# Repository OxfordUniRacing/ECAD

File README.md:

View this project on [CADLAB.io](https://cadlab.io/project/1514). 

# ECAD
Schematics and designs for the electronics team
See notes on project struture in the Oxford Uni Racing ECAD project description.
Built with EAGLE 9.2.2

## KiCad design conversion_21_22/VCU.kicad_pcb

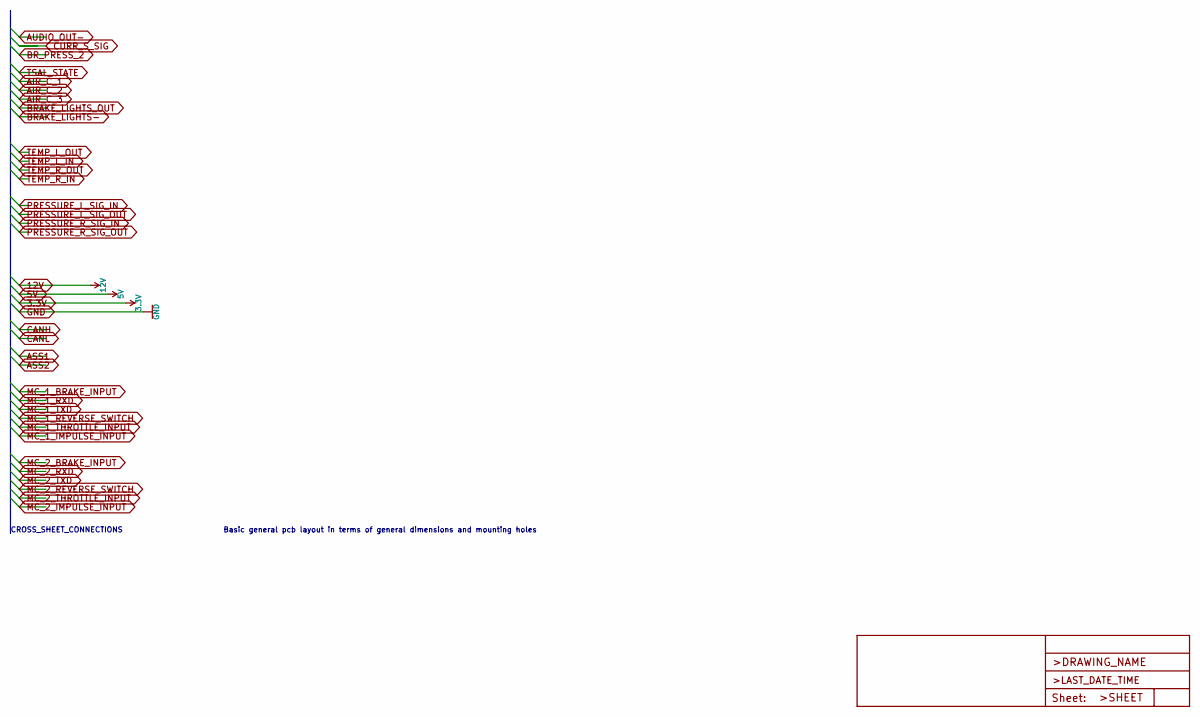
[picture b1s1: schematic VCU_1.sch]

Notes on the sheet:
Basic general pcb layout in terms of general dimensions and mounting holes
CROSS_SHEET_CONNECTIONS

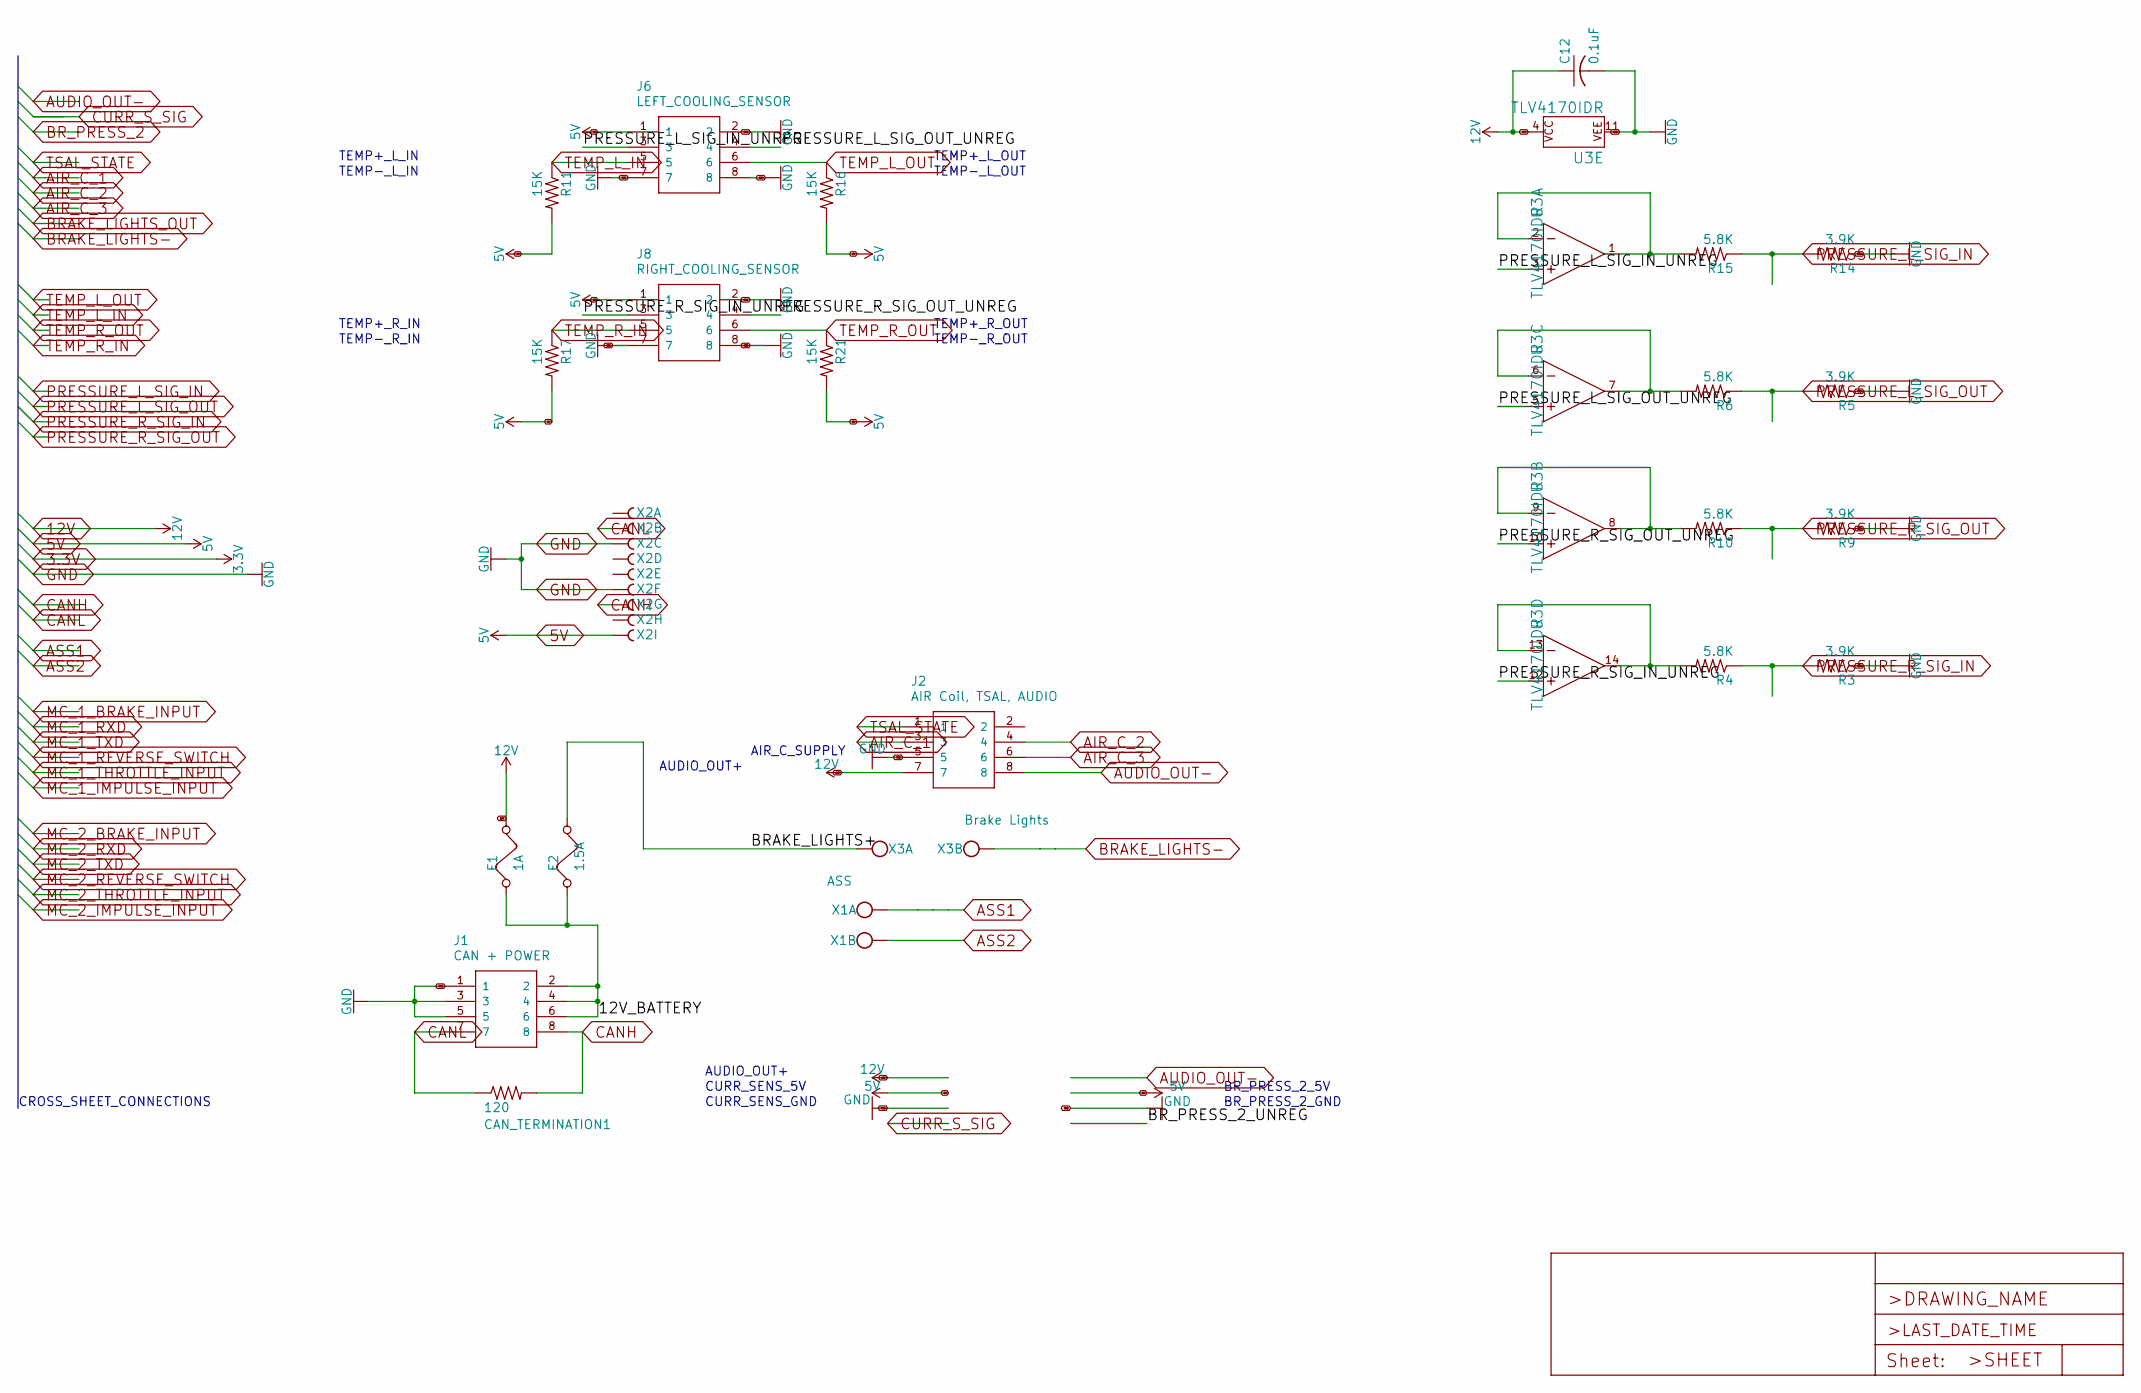
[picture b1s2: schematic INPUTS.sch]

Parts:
C12: 0.1uF; C050-024X044
CAN_TERMINATION1: 120; R0805
F1: 1A; FUSE
F2: 1.5A; FUSE
J1: CAN + POWER; HDRV8W64P254_2X4_1778X895X915P
J2: AIR Coil, TSAL, AUDIO; HDRV8W64P254_2X4_1778X895X915P
J6: LEFT_COOLING_SENSOR; HDRV8W64P254_2X4_1778X895X915P
J8: RIGHT_COOLING_SENSOR; HDRV8W64P254_2X4_1778X895X915P
R3, R5, R9, R14: 3.9K; R0805
R4, R6, R10, R15: 5.8K; R0805
R11, R16, R17, R21: 15K; R0805
U3: TLV4170IDR; SO14
X1: ASS; W237-102
X2: D-SUB9-H2M09ST; H2M09ST
X3: Brake Lights; W237-102

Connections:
5V: J6.1, J8.1, R11.2, R16.2, R17.2, R21.2, X2.9; also elsewhere on the board
12V: C12.1, F1.2, J2.7, U3.4 (P$V+); also elsewhere on the board
/INPUTS/12V_BATTERY: F1.1, F2.1, J1.2, J1.4, J1.6
/INPUTS/BRAKE_LIGHTS+: F2.2, X3.1
/INPUTS/PRESSURE_L_SIG_IN_UNREG: J6.3, U3.3 (+IN)
/INPUTS/PRESSURE_L_SIG_OUT_UNREG: J6.4, U3.5 (+IN)
/INPUTS/PRESSURE_R_SIG_IN_UNREG: J8.3, U3.12 (+IN)
/INPUTS/PRESSURE_R_SIG_OUT_UNREG: J8.4, U3.10 (+IN)
AIR_C_1: J2.3; also elsewhere on the board
AIR_C_2: J2.4; also elsewhere on the board
AIR_C_3: J2.6; also elsewhere on the board
ASS1: X1.1; also elsewhere on the board
ASS2: X1.2; also elsewhere on the board
AUDIO_OUT-: J2.8; also elsewhere on the board
BRAKE_LIGHTS-: X3.2; also elsewhere on the board
CANH: CAN_TERMINATION1.2, J1.8, X2.7; also elsewhere on the board
CANL: CAN_TERMINATION1.1, J1.7, X2.2; also elsewhere on the board
GND: C12.2, J1.1, J1.3, J1.5, J2.5, J6.2, J6.7, J6.8, J8.2, J8.7, J8.8, R3.1, R5.1, R9.1, R14.1, U3.11 (P$V-), X2.3, X2.6; also elsewhere on the board
unnamed: R4.2, U3.13 (-IN), U3.14 (OUT)
unnamed: R6.2, U3.6 (-IN), U3.7 (OUT)
unnamed: R10.2, U3.8 (OUT), U3.9 (-IN)
unnamed: R15.2, U3.1 (OUT), U3.2 (-IN)
PRESSURE_L_SIG_IN: R14.2, R15.1; also elsewhere on the board
PRESSURE_L_SIG_OUT: R5.2, R6.1; also elsewhere on the board
PRESSURE_R_SIG_IN: R3.2, R4.1; also elsewhere on the board
PRESSURE_R_SIG_OUT: R9.2, R10.1; also elsewhere on the board
TEMP_L_IN: J6.5, R11.1; also elsewhere on the board
TEMP_L_OUT: J6.6, R16.1; also elsewhere on the board
TEMP_R_IN: J8.5, R17.1; also elsewhere on the board
TEMP_R_OUT: J8.6, R21.1; also elsewhere on the board
TSAL_STATE: J2.1; also elsewhere on the board

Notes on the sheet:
CROSS_SHEET_CONNECTIONS
TEMP+_L_IN
TEMP-_L_IN
TEMP+_R_IN
TEMP-_R_IN
AIR_C_SUPPLY
CURR_SENS_5V
CURR_SENS_GND
BR_PRESS_2_5V
BR_PRESS_2_GND
AUDIO_OUT+
TEMP+_R_OUT
TEMP-_R_OUT
TEMP-_L_OUT
TEMP+_L_OUT

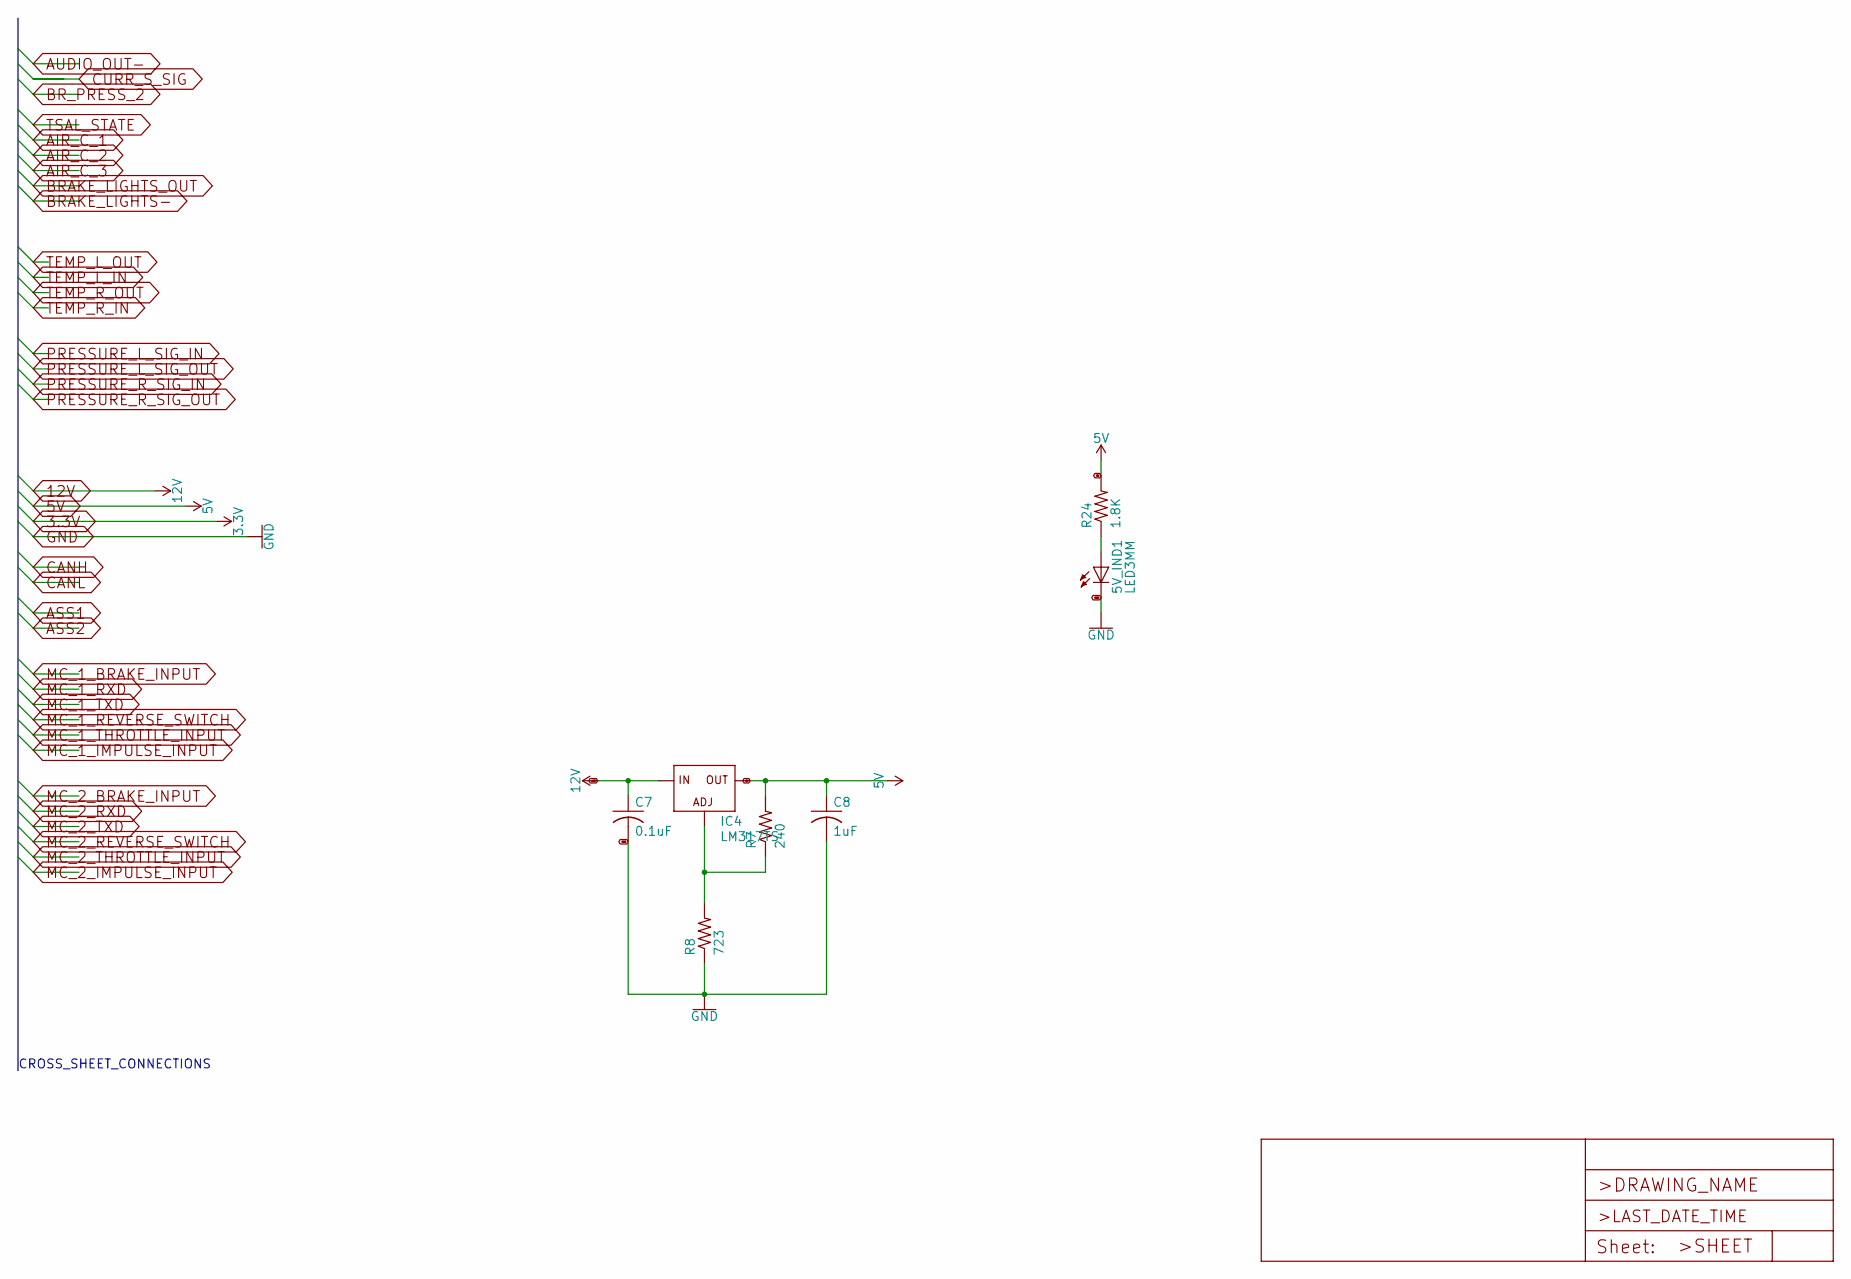
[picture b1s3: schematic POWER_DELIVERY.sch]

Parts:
5V_IND: LED3MM
C7: 0.1uF; C050-025X075
C8: 1uF; C050-025X075
IC4: LM317TS; 317TS
R7: 240; R0805
R8: 723; R0805
R24: 1.8K; R0805

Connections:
5V: C8.1, IC4.2 (OUT), R7.2, R24.2; also elsewhere on the board
12V: C7.1, IC4.3 (IN); also elsewhere on the board
GND: C7.2, C8.2, R8.1; also elsewhere on the board
unnamed 35: R24.1; also elsewhere on the board
unnamed: IC4.1 (ADJ), R7.1, R8.2

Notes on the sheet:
CROSS_SHEET_CONNECTIONS

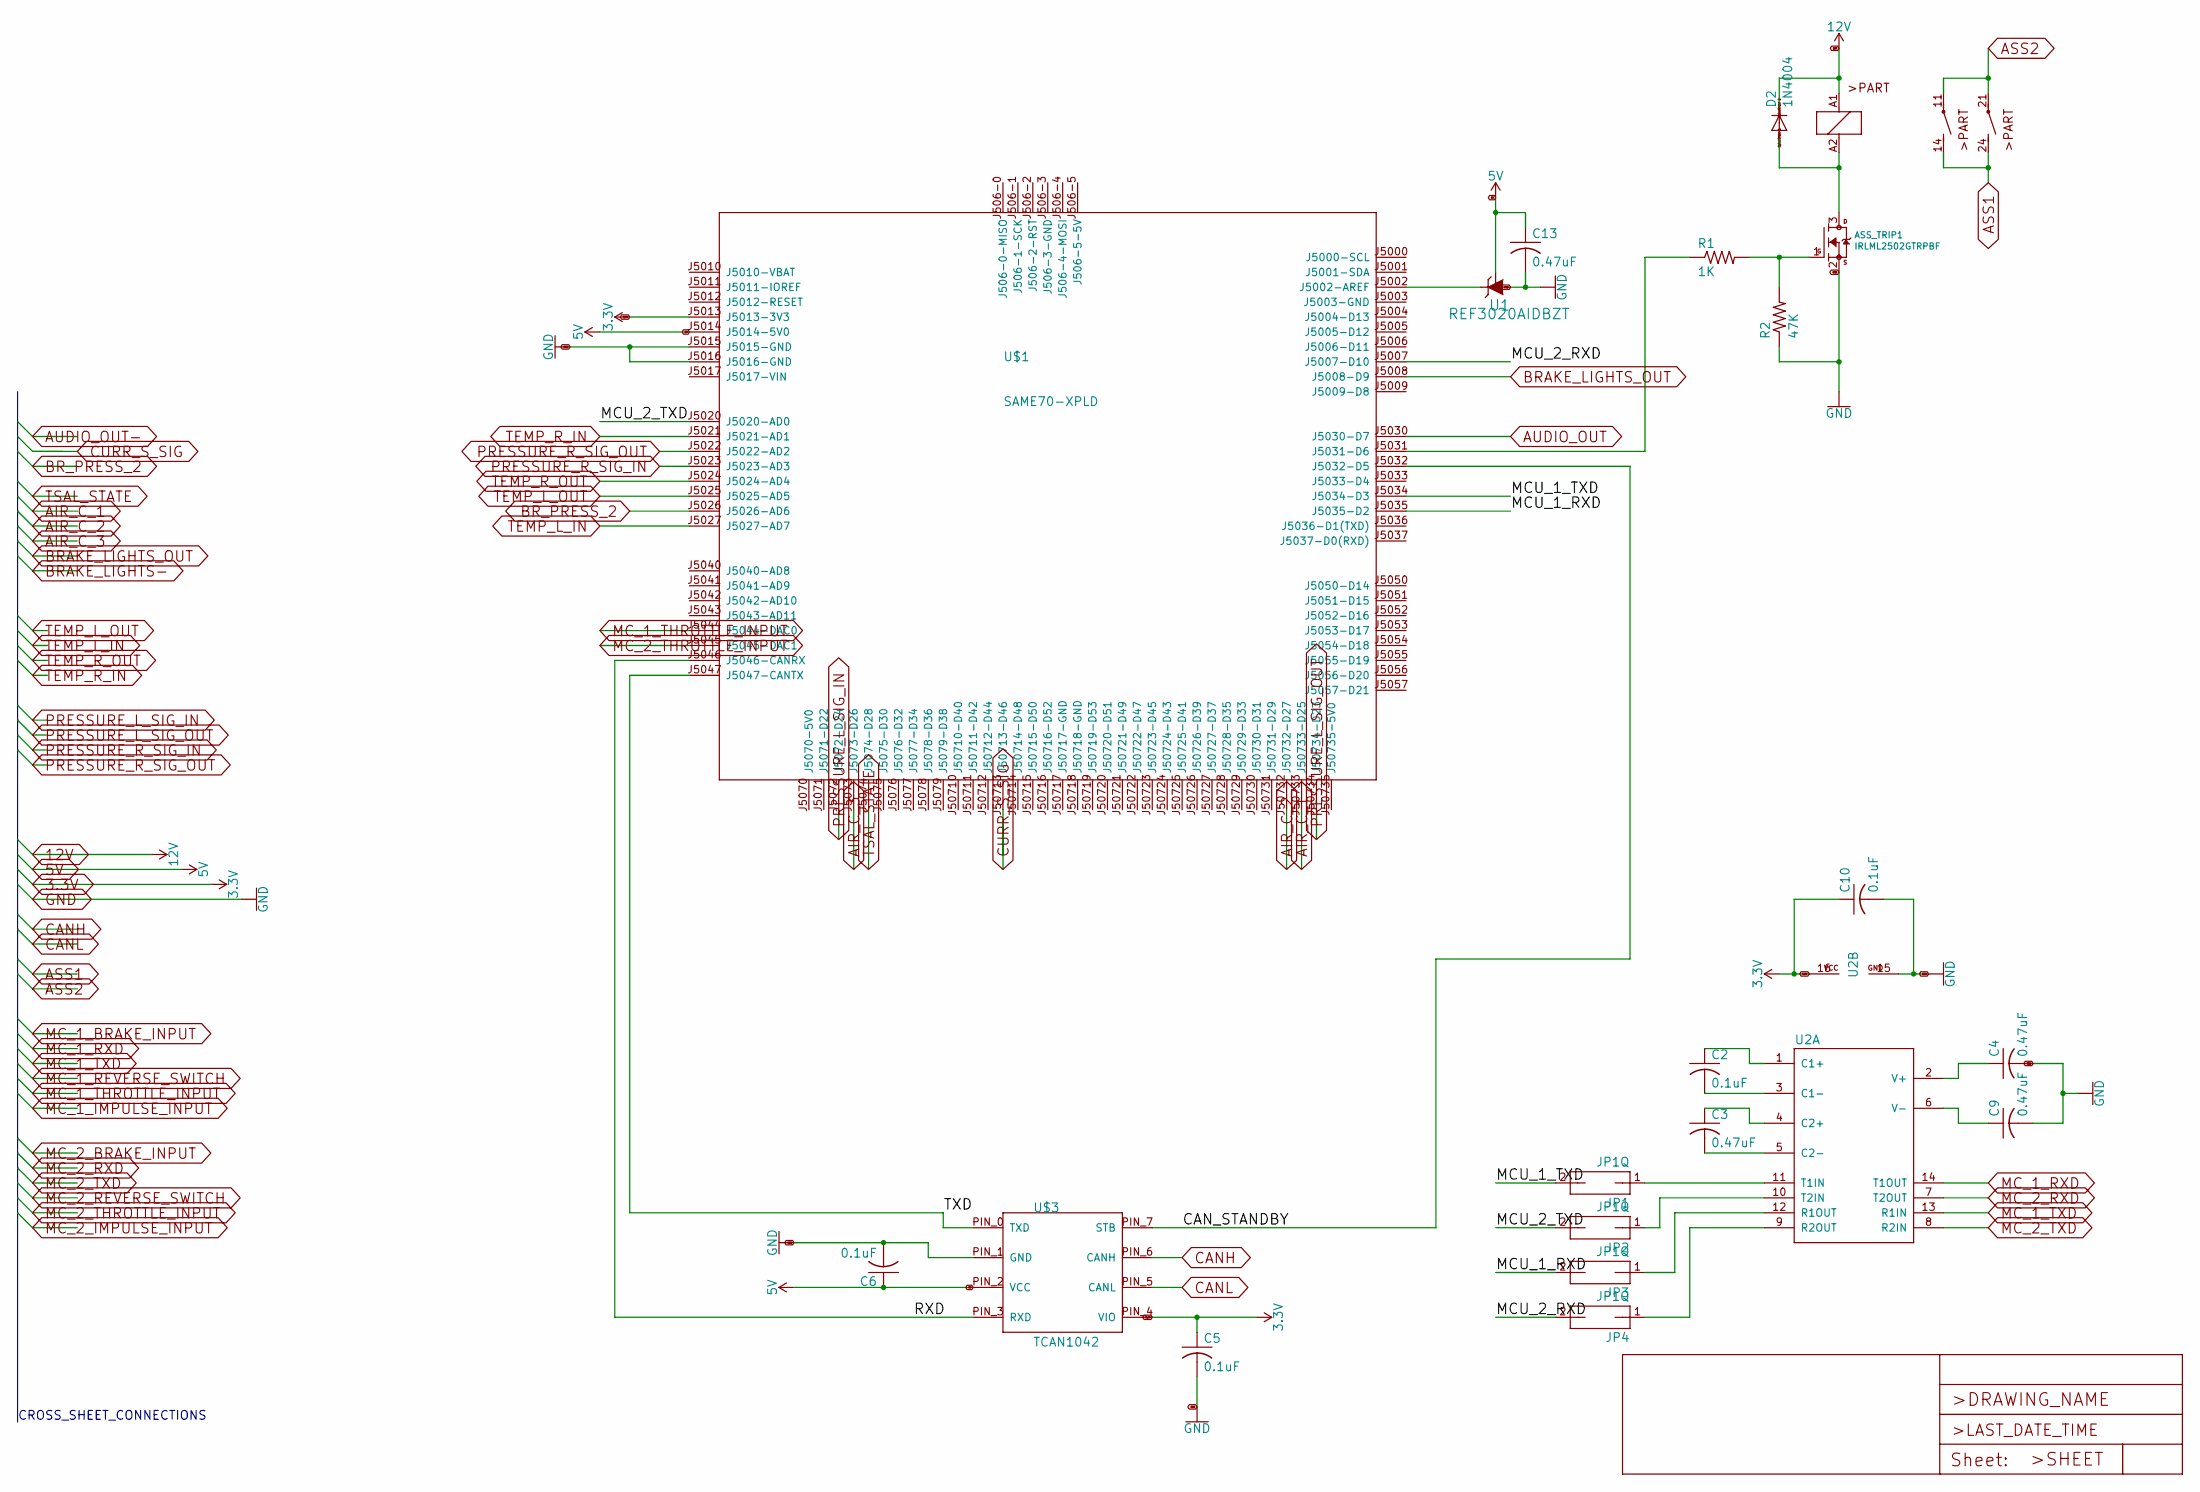
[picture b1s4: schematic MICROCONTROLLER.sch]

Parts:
ASS_TRIP: IRLML2502GTRPBF; SOT23
C2, C5, C6, C10: 0.1uF; C025-024X044
C3, C4, C9: 0.47uF; C025-024X044
C13: 0.47uF; C050-024X044
D2: 1N4004; DO41-10
JP1, JP2, JP3, JP4: JP1Q; JP1
K1: RT44?4; RT2N_O
R1: 1K; R0805
R2: 47K; R0805
U1: REF3020AIDBZT; SOT23-3
U2: MAX3232S; SO16
U$1: SAME70-XPLD
U$3: TCAN1042

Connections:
3.3V: C5.1, C10.1, U2.16 (VCC), U$1.J5013 (J5013-3V3), U$3.PIN_4 (VIO)
5V: C6.1, C13.1, U1.1 (ADJ), U$1.J5014 (J5014-5V0), U$3.PIN_2 (VCC); also elsewhere on the board
12V: D2.C, K1.A1 (1); also elsewhere on the board
/MICROCONTROLLER/CAN_STANDBY: U$1.J5032 (J5032-D5), U$3.PIN_7 (STB)
/MICROCONTROLLER/MCU_1_RXD: JP3.2, U$1.J5035 (J5035-D2)
/MICROCONTROLLER/MCU_1_TXD: JP1.2, U$1.J5034 (J5034-D3)
/MICROCONTROLLER/MCU_2_RXD: JP4.2, U$1.J5007 (J5007-D10)
/MICROCONTROLLER/MCU_2_TXD: JP2.2, U$1.J5020 (J5020-AD0)
/MICROCONTROLLER/RXD: U$1.J5046 (J5046-CANRX), U$3.PIN_3 (RXD)
/MICROCONTROLLER/TXD: U$1.J5047 (J5047-CANTX), U$3.PIN_0 (TXD)
AIR_C_1: U$1.J50733 (J50733-D25); also elsewhere on the board
AIR_C_2: U$1.J50732 (J50732-D27); also elsewhere on the board
AIR_C_3: U$1.J5073 (J5073-D26); also elsewhere on the board
ASS1: K1.14 (S), K1.24 (S); also elsewhere on the board
ASS2: K1.11, K1.21; also elsewhere on the board
AUDIO_OUT: U$1.J5030 (J5030-D7); also elsewhere on the board
BRAKE_LIGHTS_OUT: U$1.J5008 (J5008-D9); also elsewhere on the board
BR_PRESS_2: U$1.J5026 (J5026-AD6)
CANH: U$3.PIN_6 (CANH); also elsewhere on the board
CANL: U$3.PIN_5 (CANL); also elsewhere on the board
GND: C4.2, C5.2, C6.2, C9.2, C10.2, C13.2, R2.1, U1.3 (A), U2.15 (GND), U$1.J5015 (J5015-GND), U$1.J5016 (J5016-GND), U$3.PIN_1 (GND); also elsewhere on the board
MC_1_RXD: U2.14 (T1OUT); also elsewhere on the board
MC_1_THROTTLE_INPUT: U$1.J5044 (J5044-DAC0)
MC_1_TXD: U2.13 (R1IN); also elsewhere on the board
MC_2_RXD: U2.7 (T2OUT); also elsewhere on the board
MC_2_THROTTLE_INPUT: U$1.J5045 (J5045-DAC1)
MC_2_TXD: U2.8 (R2IN); also elsewhere on the board
unnamed 36: R1.2, R2.2; also elsewhere on the board
unnamed 37: D2.A, K1.A2 (2); also elsewhere on the board
unnamed: C2.1, U2.1 (C1+)
unnamed: C2.2, U2.3 (C1-)
unnamed: C3.1, U2.4 (C2+)
unnamed: C3.2, U2.5 (C2-)
unnamed: C4.1, U2.2 (V+)
unnamed: C9.1, U2.6 (V-)
unnamed: JP1.1, U2.11 (T1IN)
unnamed: JP2.1, U2.10 (T2IN)
unnamed: JP3.1, U2.12 (R1OUT)
unnamed: JP4.1, U2.9 (R2OUT)
unnamed: R1.1, U$1.J5031 (J5031-D6)
unnamed: U1.2 (C), U$1.J5002 (J5002-AREF)
PRESSURE_L_SIG_IN: U$1.J5072 (J5072-D24); also elsewhere on the board
PRESSURE_L_SIG_OUT: U$1.J50734 (J50734-D23); also elsewhere on the board
PRESSURE_R_SIG_IN: U$1.J5023 (J5023-AD3); also elsewhere on the board
PRESSURE_R_SIG_OUT: U$1.J5022 (J5022-AD2); also elsewhere on the board
TEMP_L_IN: U$1.J5027 (J5027-AD7); also elsewhere on the board
TEMP_L_OUT: U$1.J5025 (J5025-AD5); also elsewhere on the board
TEMP_R_IN: U$1.J5021 (J5021-AD1); also elsewhere on the board
TEMP_R_OUT: U$1.J5024 (J5024-AD4); also elsewhere on the board
TSAL_STATE: U$1.J5074 (J5074-D28); also elsewhere on the board

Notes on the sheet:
CROSS_SHEET_CONNECTIONS

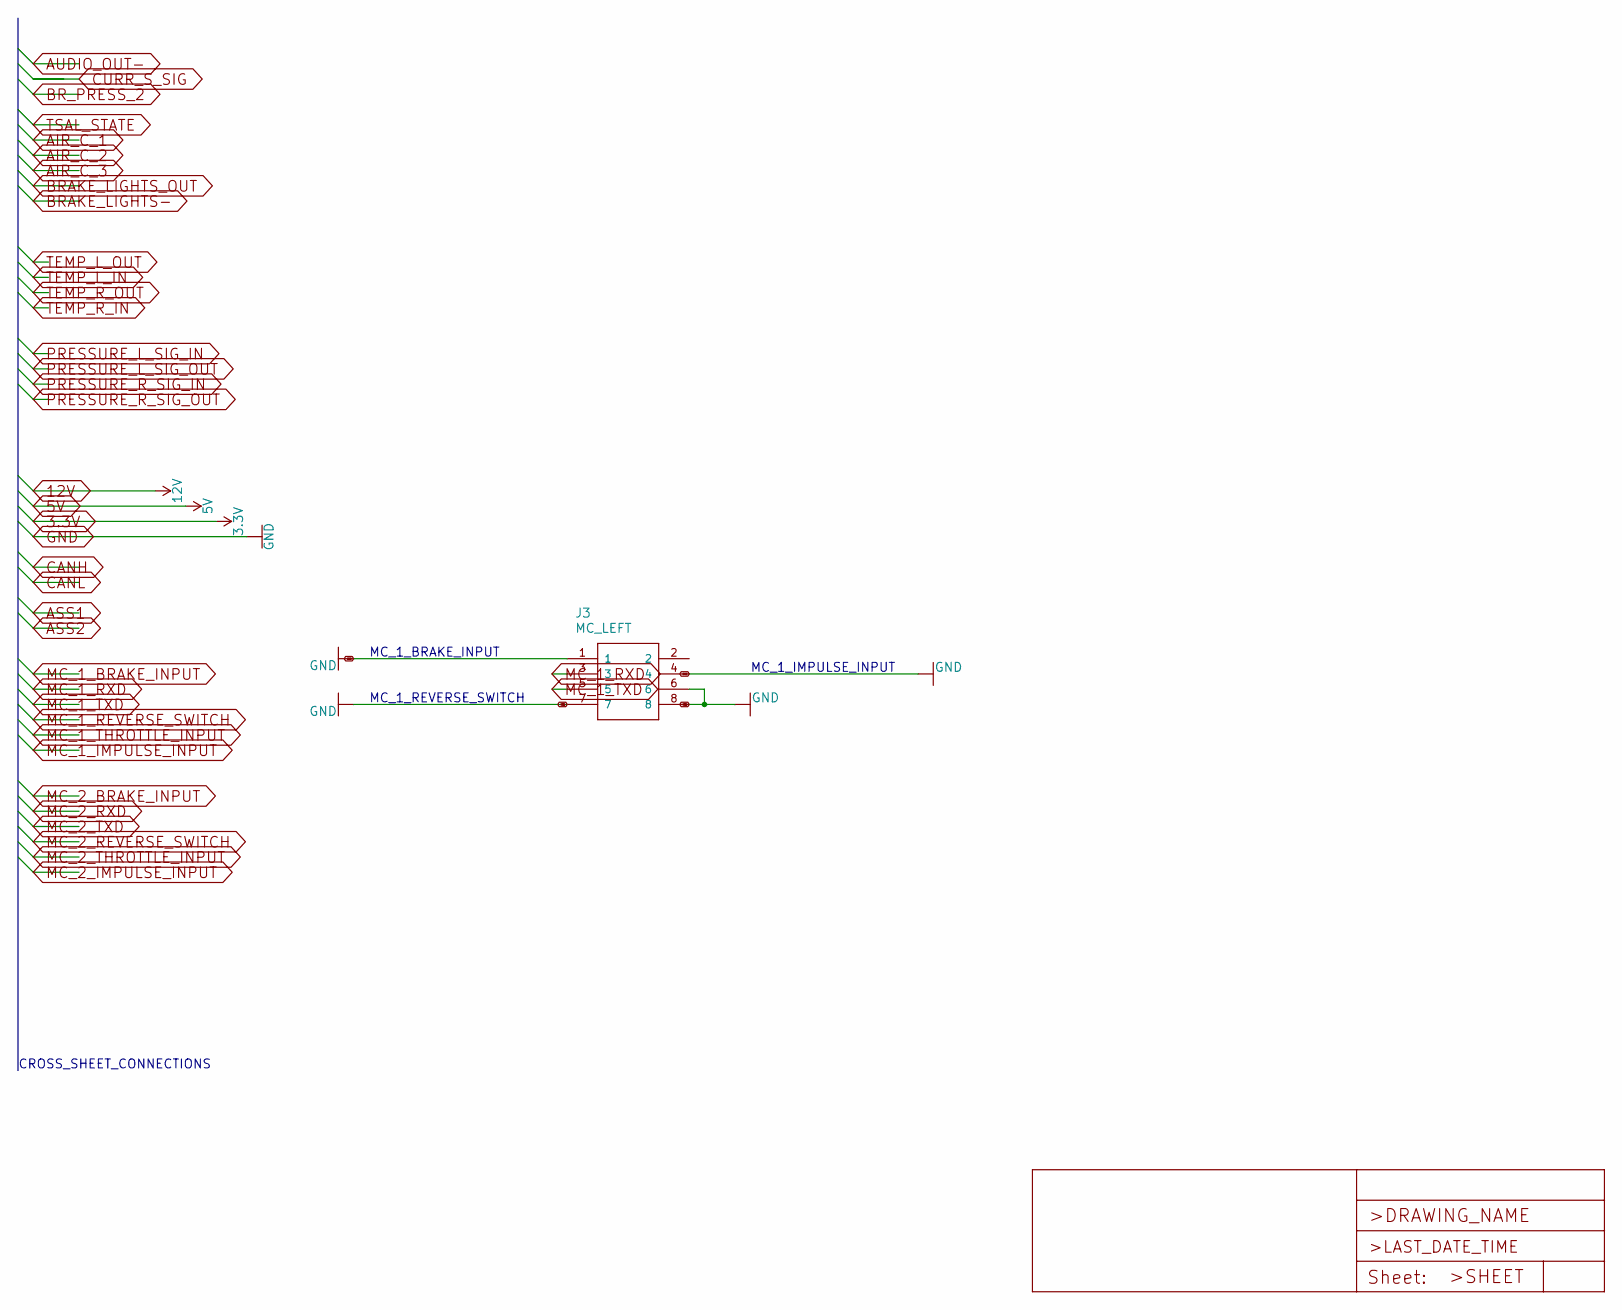
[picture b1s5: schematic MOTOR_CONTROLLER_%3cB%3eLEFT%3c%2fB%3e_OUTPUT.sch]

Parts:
J3: MC_LEFT; HDRV8W64P254_2X4_1778X895X915P

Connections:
GND: J3.1, J3.4, J3.6, J3.7, J3.8; also elsewhere on the board
MC_1_RXD: J3.3; also elsewhere on the board
MC_1_TXD: J3.5; also elsewhere on the board

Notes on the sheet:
MC_1_BRAKE_INPUT
MC_1_REVERSE_SWITCH
MC_1_IMPULSE_INPUT
CROSS_SHEET_CONNECTIONS

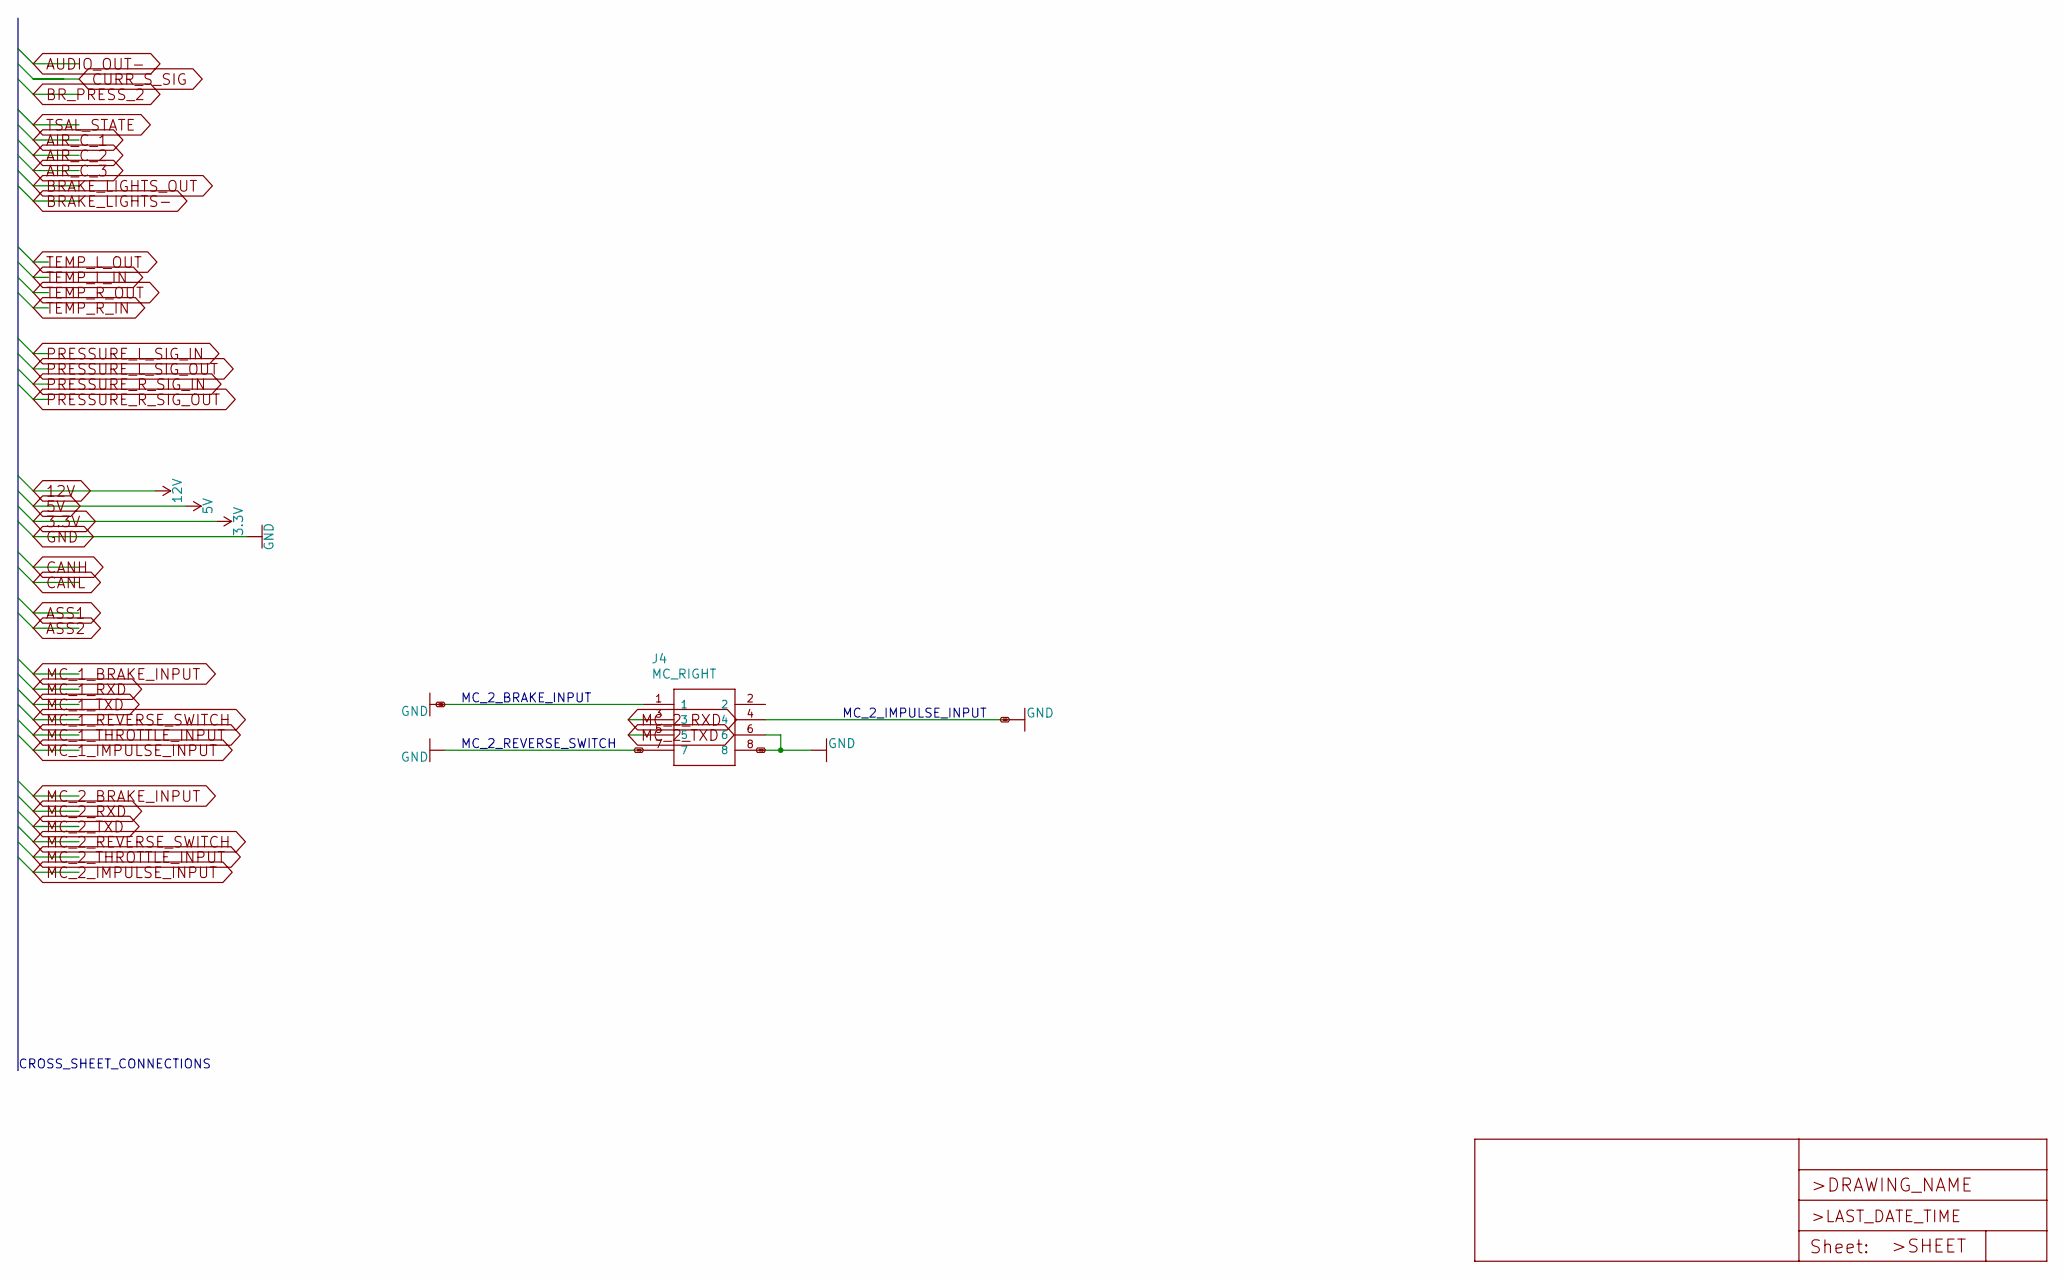
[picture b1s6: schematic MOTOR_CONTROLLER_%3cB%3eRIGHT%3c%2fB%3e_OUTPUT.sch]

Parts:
J4: MC_RIGHT; HDRV8W64P254_2X4_1778X895X915P

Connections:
GND: J4.1, J4.4, J4.6, J4.7, J4.8; also elsewhere on the board
MC_2_RXD: J4.3; also elsewhere on the board
MC_2_TXD: J4.5; also elsewhere on the board

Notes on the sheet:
MC_2_BRAKE_INPUT
MC_2_REVERSE_SWITCH
MC_2_IMPULSE_INPUT
CROSS_SHEET_CONNECTIONS

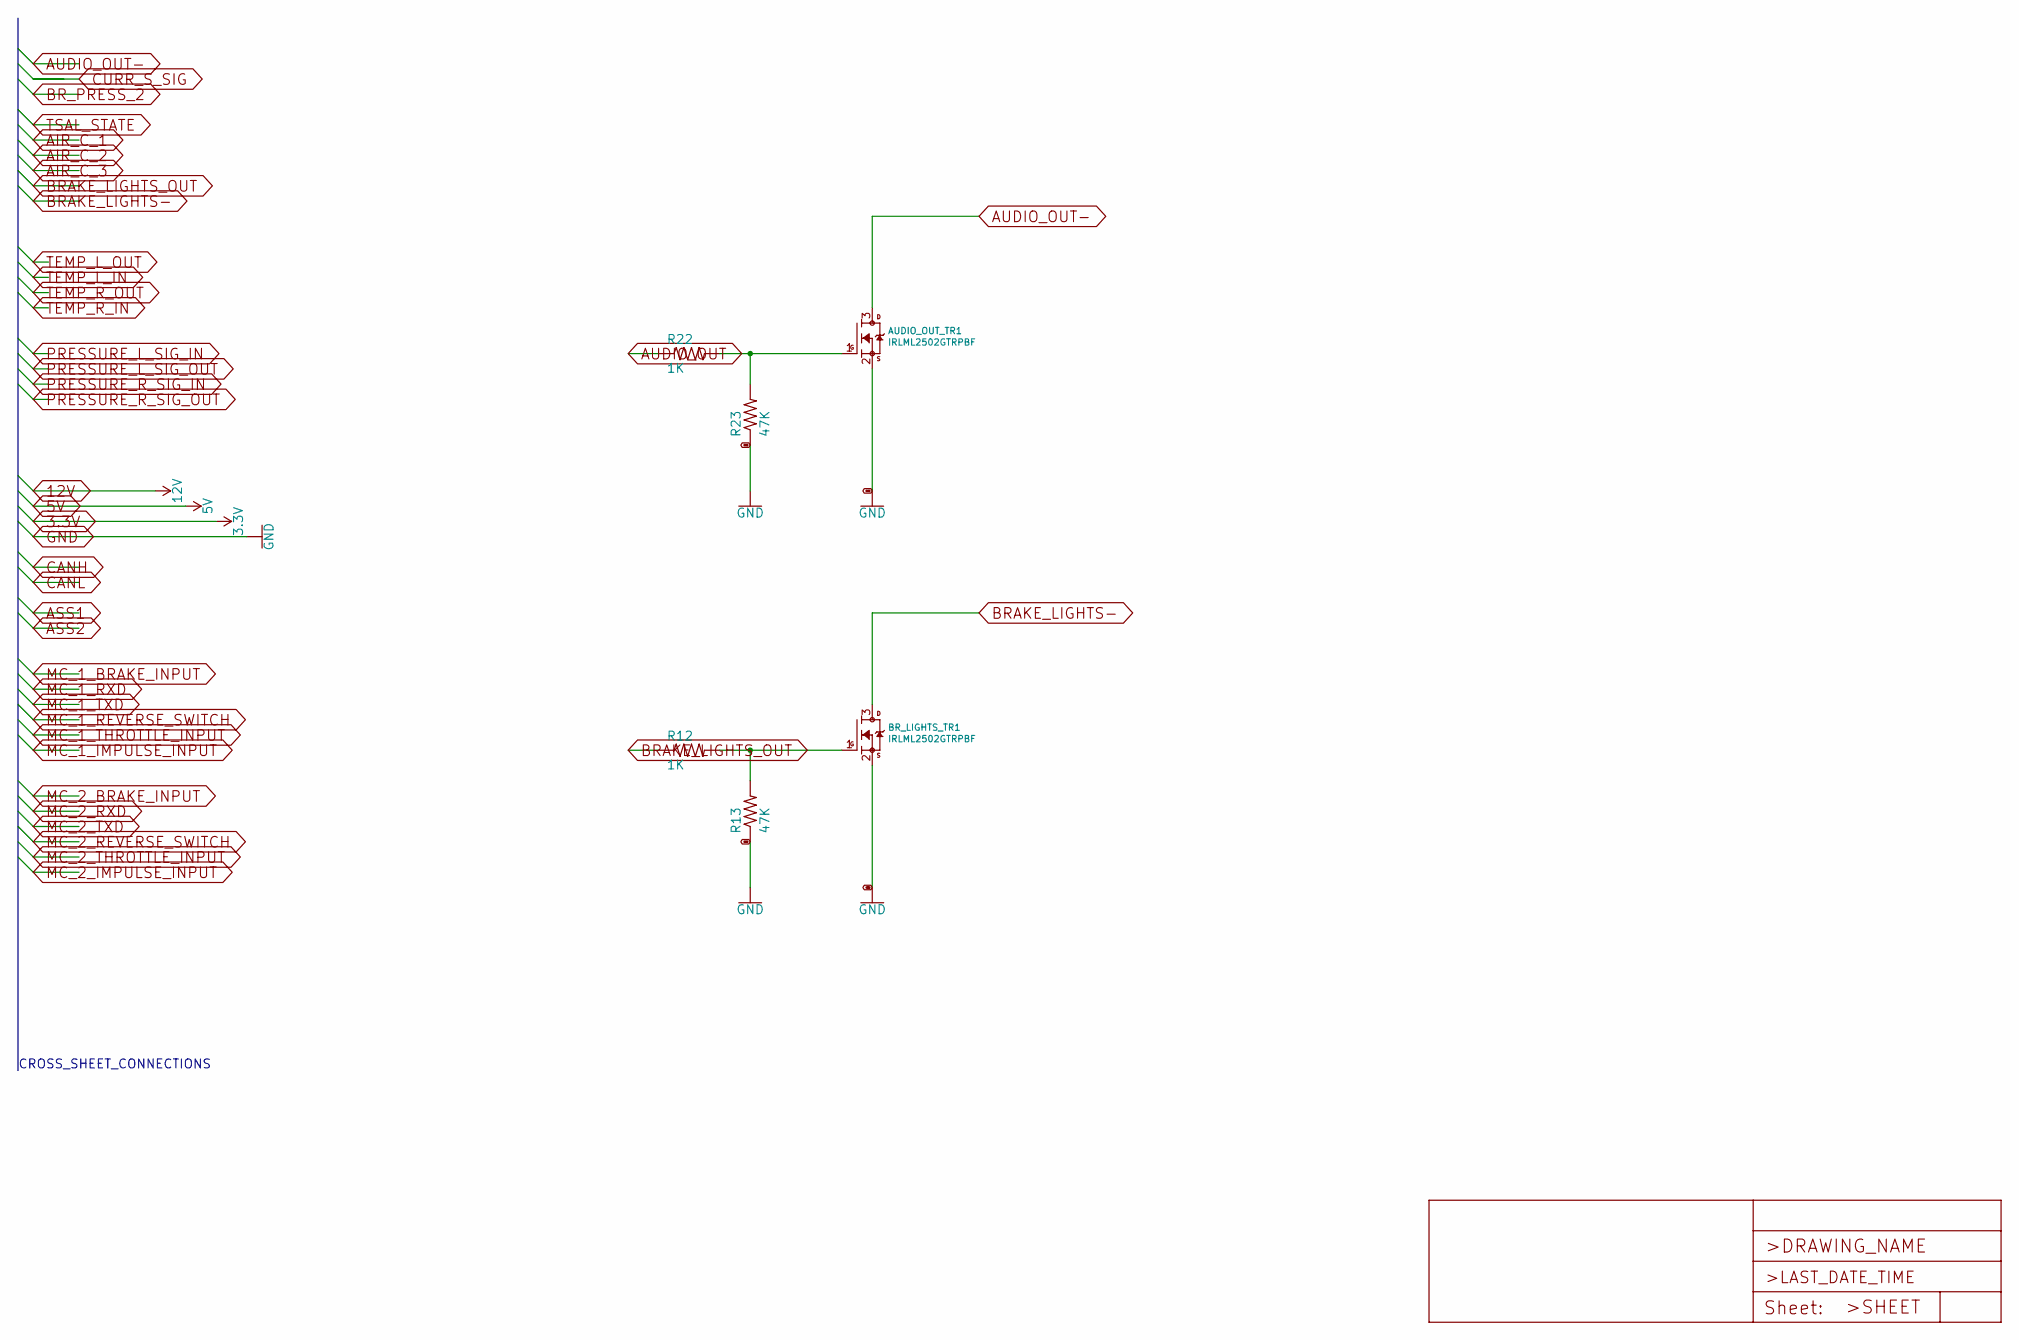
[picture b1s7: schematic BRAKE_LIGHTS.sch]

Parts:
AUDIO_OUT_TR: IRLML2502GTRPBF; SOT23
BR_LIGHTS_TR1: IRLML2502GTRPBF; SOT23
R12, R22: 1K; R0805
R13, R23: 47K; R0805

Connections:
AUDIO_OUT: R22.1; also elsewhere on the board
BRAKE_LIGHTS-: BR_LIGHTS_TR1.3 (D); also elsewhere on the board
BRAKE_LIGHTS_OUT: R12.1; also elsewhere on the board
GND: BR_LIGHTS_TR1.2 (S), R13.1, R23.1; also elsewhere on the board
unnamed 38: R22.2, R23.2; also elsewhere on the board
unnamed: BR_LIGHTS_TR1.1 (G), R12.2, R13.2

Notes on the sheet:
CROSS_SHEET_CONNECTIONS

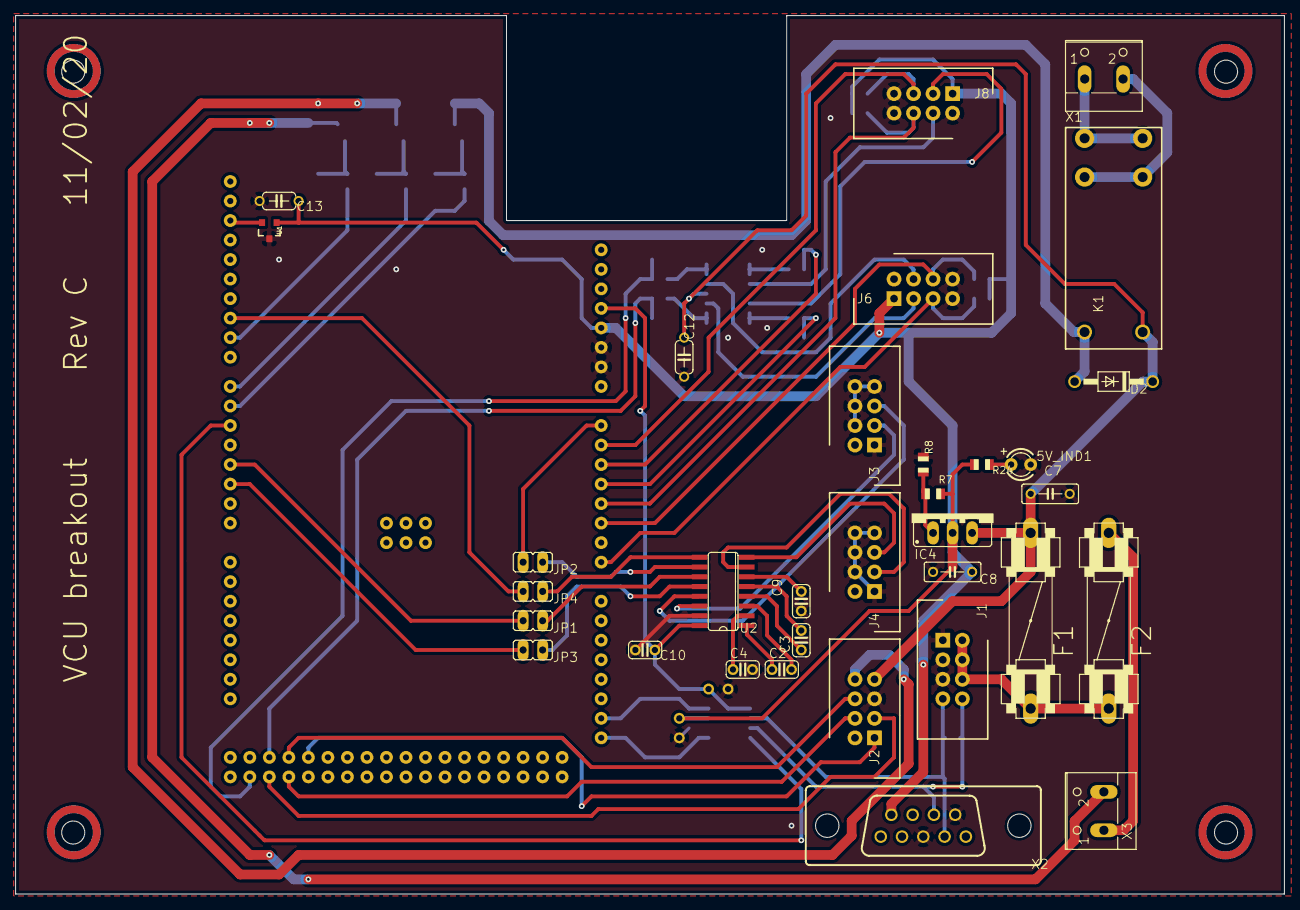
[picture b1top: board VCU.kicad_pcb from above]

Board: 2 copper layers, 165.1 x 114.3 mm, 64 parts (0 on the bottom side), 63 nets.

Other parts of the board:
5V_IND1: LED3MM
@HOLE0, @HOLE1, @HOLE2, @HOLE3: (no value)
ASS_TRIP1: IRLML2502GTRPBF; SOT23
AUDIO_OUT_TR1: IRLML2502GTRPBF; SOT23

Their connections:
AUDIO_OUT-: AUDIO_OUT_TR1.3; also elsewhere on the board
GND: 5V_IND1.K, ASS_TRIP1.2, AUDIO_OUT_TR1.2; also elsewhere on the board
unnamed 35: 5V_IND1.A; also elsewhere on the board
unnamed 36: ASS_TRIP1.1; also elsewhere on the board
unnamed 37: ASS_TRIP1.3; also elsewhere on the board
unnamed 38: AUDIO_OUT_TR1.1; also elsewhere on the board
